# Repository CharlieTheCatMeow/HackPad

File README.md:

# (i)Pad
 ~~Trying to create a Hackpad.
 I'm new to this, so I'm just trying things out at this stage.~~ <br>
 I created a Macropad. I figured it out :D <br>

## What is the (i)Pad?
The (i)Pad is a Macropad built for productivity work. It was designed by me and 13 hours of my time. It runs on QMK firmware.

## What is included in the (i)Pad:
- 8 keys
- one rotary encoder
- one OLED display
- 6 LEDs

## Firmware:
The keyboard runs on QMK firmware. There are 4 layers in total. The layer is visible on the OLED screen. There is also a layer indicator on the first LED, it changes color. The other 5 LED's play a little animation when you click the keys. 
Everything should work as expected. 

## The finished product:

## The Shell:

## The PCB:

## The Production files:
[(i)Pad production files](Production)

## This project took me around 20 hours and I'm glad it's (hopefully) done
I chose this project as a kind of first step into electronics and CAD.
I learned how to use KiCAD and create firmware and got better at Fusion. 
Soldering wasn't as difficult as I thought it would be. The firmware was a bit hard to set up, but it works.
Overall a great project and I'm fairly happy with the result.

## BOM:
- 8x MX Switches
- 1x Rotary Encoder
- 6x LED
- 1x PCB
- 1x OLED screen
- 1x Shell
- 1x Plate
- 1x RP2040 controller
- 9x Diode

**Credits:**
 Used AI for basic questions about the firmware and hardware

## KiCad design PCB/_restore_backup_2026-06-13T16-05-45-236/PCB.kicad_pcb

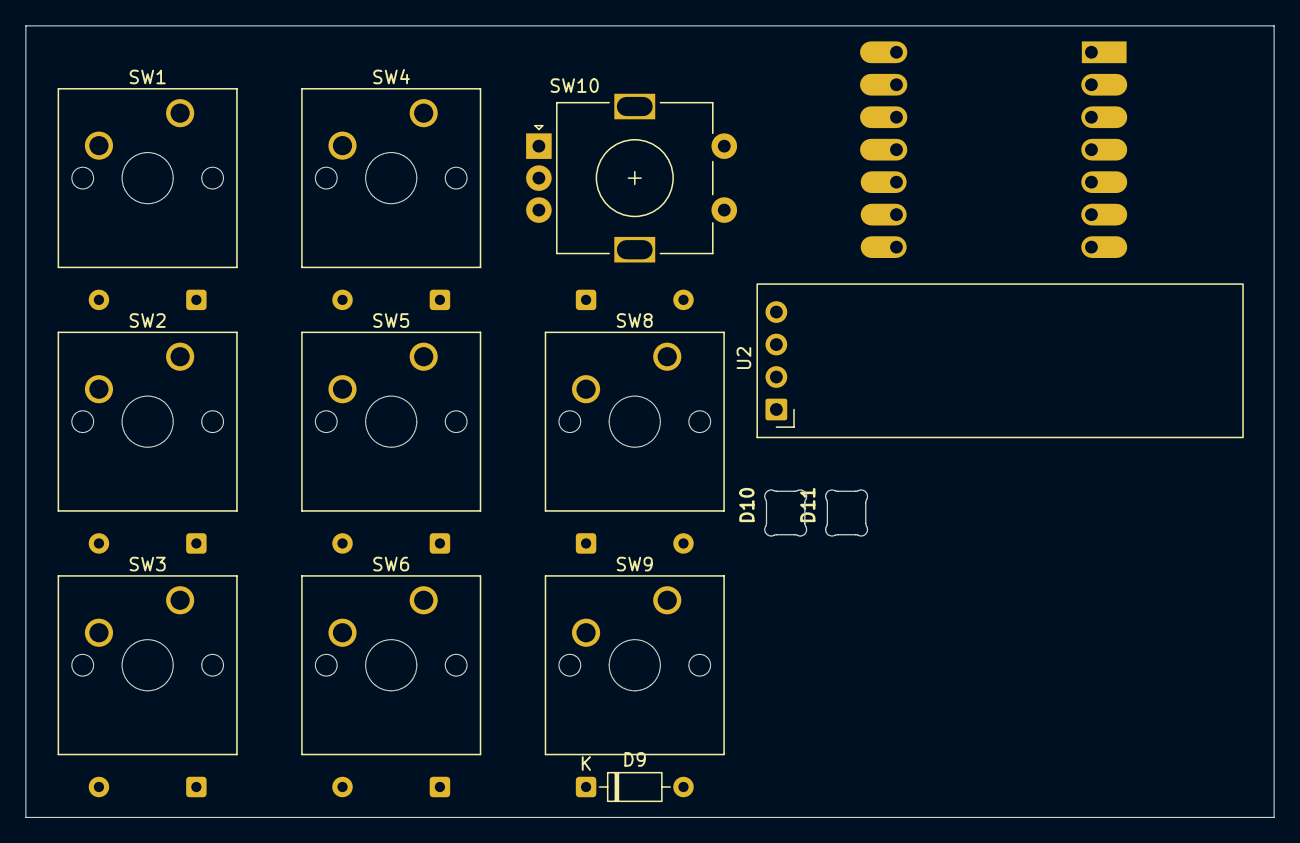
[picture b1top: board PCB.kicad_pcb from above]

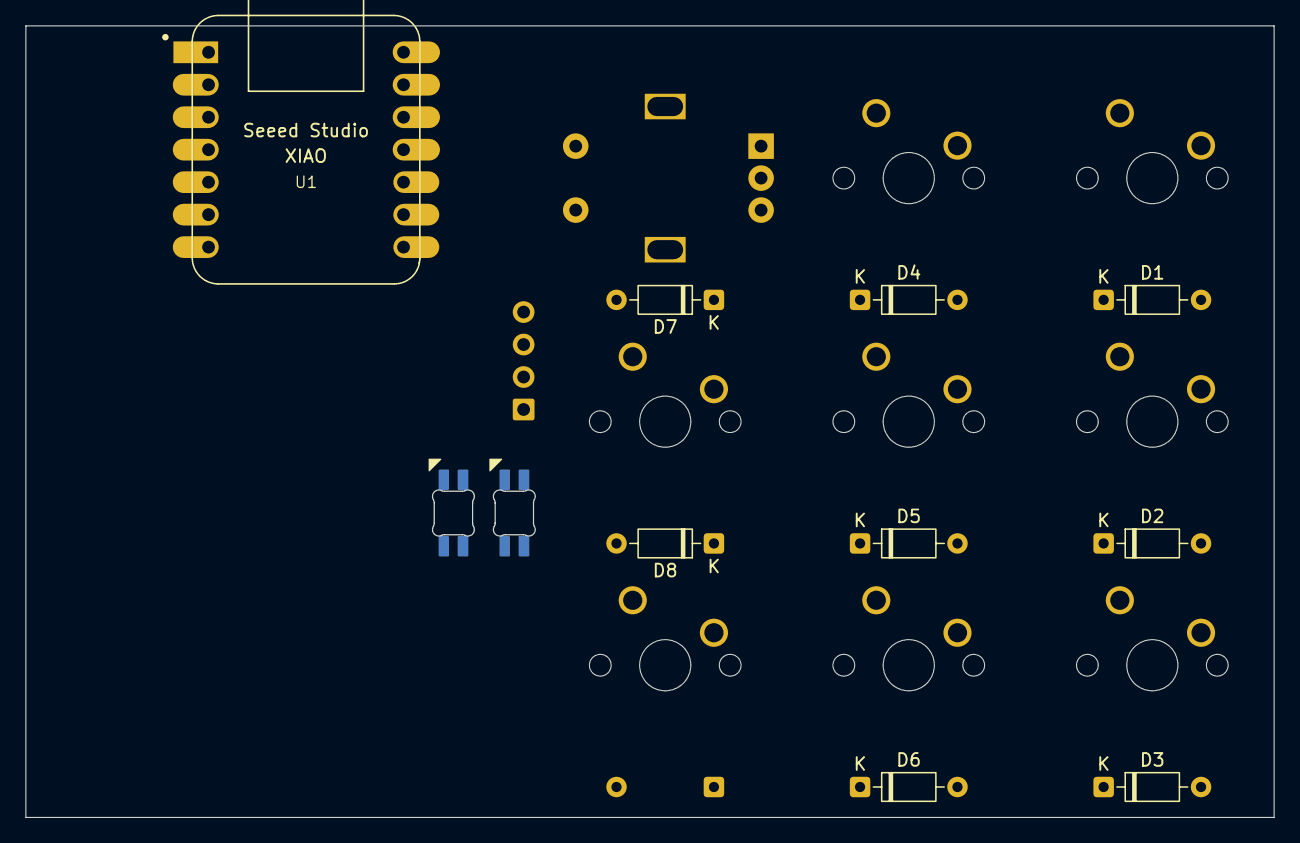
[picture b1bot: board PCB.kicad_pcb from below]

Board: 2 copper layers, 97.6 x 61.9 mm, 22 parts (9 on the bottom side), 23 nets, no tracks yet.

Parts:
D1, D2, D3, D4, D5, D6, D7, D8, D9: 1N4148; D_DO-35_SOD27_P7.62mm_Horizontal
D10, D11: SK6812MINI-E; SK6812MINI-E_fixed
SW1, SW2, SW3, SW4, SW5, SW6, SW8, SW9: SW_Push; SW_Cherry_MX_1.00u_PCB
SW10: RotaryEncoder_Switch; RotaryEncoder_Alps_EC11E-Switch_Vertical_H20mm
U1: MOUDLE-SEEEDUINO-XIAO; XIAO-Generic-Hybrid-14P-2.54-21X17.8MM
U2: ER_OLEDM0.91_1x-I2C

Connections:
5V: D10.1 (VDD), D11.1 (VDD), U1.14 (5V), U2.2 (VCC)
Column 1: D1.1 (K), D2.1 (K), D3.1 (K), U1.8 (PB09_A7_D7_RX)
Column 2: D4.1 (K), D5.1 (K), D6.1 (K), U1.3 (PA10_A2_D2)
Column 3: D7.1 (K), D8.1 (K), D9.1 (K), U1.4 (PA11_A3_D3)
Encoder A: SW10.A, U1.2 (PA4_A1_D1)
Encoder B: SW10.B, U1.1 (PA02_A0_D0)
GND: D10.3 (VSS), D11.3 (VSS), SW10.C, U1.13 (GND), U2.1 (GND)
LED Data: D10.4 (DIN), U1.7 (PB08_A6_D6_TX)
unnamed: D1.2 (A), SW1.2
unnamed: D2.2 (A), SW2.2
unnamed: D3.2 (A), SW3.2
unnamed: D4.2 (A), SW4.2
unnamed: D5.2 (A), SW5.2
unnamed: D6.2 (A), SW6.2
unnamed: D7.2 (A), SW10.S1
unnamed: D8.2 (A), SW8.2
unnamed: D9.2 (A), SW9.2
unnamed: D10.2 (DOUT), D11.4 (DIN)
Row 1: SW3.1, SW6.1, SW9.1, U1.9 (PA7_A8_D8_SCK)
Row 2: SW2.1, SW5.1, SW8.1, U1.10 (PA5_A9_D9_MISO)
Row 3: SW1.1, SW4.1, SW10.S2, U1.11 (PA6_A10_D10_MOSI)
SCL: U1.6 (PA9_A5_D5_SCL), U2.3 (SCL)
SDA: U1.5 (PA8_A4_D4_SDA), U2.4 (SDA)
